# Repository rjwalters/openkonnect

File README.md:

# openkonnect

An MIT-licensed MCP server that lets an LLM agent drive a **running KiCad 10**:
schematic, layout, placement, routing, design review and manufacturing tools,
through KiCad's IPC API.

> **Status: Phase 0 bootstrap.** The MCP server runs and exposes read-only
> tools that inspect the session and the open board, plus the save, sync and
> handoff tools that write files or reload the editor (see [Tools](#tools)).
> See [ROADMAP.md](ROADMAP.md) for the plan and
> [spec/capabilities.md](spec/capabilities.md) for what each tool does.

## Quickstart

**1. Install.** You need [uv](https://docs.astral.sh/uv/) and Python 3.10 or
newer.

```bash
git clone https://github.com/rjwalters/openkonnect
cd openkonnect
uv sync
uv run openkonnect --version
```

**2. Turn on KiCad's API server.** In KiCad 10, open *Preferences > Plugins*,
check **Enable KiCad API**, and restart KiCad. The API is off by default.
Then open your board in the PCB editor. Check the connection with:

```bash
uv run openkonnect status
```

It prints `session_status` as JSON. `"ipc_reachable": true` means the server
can reach KiCad. Otherwise `reason` says what is wrong, for example
`kicad_not_running` or `ipc_disabled`.

**3. Register the server with your MCP client.** The server speaks MCP over
stdio. For Claude Code, run:

```bash
claude mcp add openkonnect -- uv run --directory /path/to/openkonnect openkonnect serve
```

For clients configured with JSON (Claude Desktop, Cursor and similar):

```json
{
  "mcpServers": {
    "openkonnect": {
      "command": "uv",
      "args": ["run", "--directory", "/path/to/openkonnect", "openkonnect", "serve"],
      "env": { "OPENKONNECT_TIMEOUT": "5" }
    }
  }
}
```

### Tools

| Tool | Spec | What it returns |
|------|------|-----------------|
| `session_status` | SES-01 | Whether KiCad is running and its API reachable, versions, instance, project directory, open documents with dirty state, and which tools this instance supports. "Not running" and "API disabled" come back as data, not errors. |
| `list_instances` | SES-02 | Every KiCad instance whose API socket can be found: endpoint, process id, whether it answered, KiCad version, open board path, and why not if it did not answer. No sockets is an empty list; a platform that cannot list sockets says `listable: false`. Sockets are probed one at a time, each bounded by the call timeout. |
| `board_summary` | LAY-01 | Live overview of the open board, unsaved changes included: path, title block, layer counts, counts of footprints, nets, tracks, vias and zones, outline size, dirty state. |
| `board_outline` | LAY-08 | The outline of the open board, unsaved changes included: the closed polygons that make it up (file frame, mm, each with a role of `outline` or `hole`), the extents, the board-frame offset and KiCad's grid and drill origins in both frames. Arcs and circles are sampled into segments. No Edge.Cuts shapes is `present: false`; shapes that do not close are `closed: false` with the open chains and the gap that defeated them, never a rectangle. |
| `list_footprints` | LAY-02 | Live list of the board's footprints, unsaved changes included: refdes, value, library ID, position (file and board frames, with the offset between them), rotation, side, locked, attributes and fields. Optional filters: `refs`, `side`, `box` (frame required), `selected_only`; a filter matching nothing is an empty list. |
| `footprint_pads` | LAY-03 | Live pads of the footprints named in `refs` (`R1` for all its pads, `R1.2` for one), unsaved changes included: `REF.PAD`, number, net, position (file and board frames, with the offset), layers, shape and size. An unknown reference or pad is `not_found`; a net that cannot be read is `net: null` with `net_state: "unknown"` and a reason, never unconnected. |
| `get_selection` | SES-08 | What is selected in the PCB editor, as file-level references `kct` accepts (reference designators, `REF.PAD`, nets), plus other items with session-scoped ids and the selection's bounding box. An empty selection is an ordinary result. |
| `list_nets` | LAY-04 | The nets on the open board with each net's net class and pad count; optional glob `pattern` and `net_class` filters. `include_items` adds the items on each net (pads as `REF.PAD`, other copper with session ids) and needs KiCad 10.0.1, else `unsupported_on_this_kicad`. |
| `list_zones` | LAY-06 | The copper zones and rule areas on the open board, unsaved changes included: session id, name, net, layers, priority, pad-connection style, filled and locked state; a rule area also lists what it keeps out. Optional `net` and `layer` filters; a filter matching nothing is an empty list, an unknown layer is `invalid_argument`. |
| `show_findings` | SES-09 | Selects in the editor the items that kicad-tools findings (`kct ... --format json`) point at, and reports per finding what resolved, what did not and why, and which findings may be stale. |
| `save_before_external_write` | SES-04 | Before a `kct` command touches the open board: each document's state before, the action taken (none, saved or refused), and the file and editor hashes to pass to `sync_from_disk`. Refuses a dirty or unknown board unless `allow_save`. See [the handoff protocol](docs/handoff-protocol.md). |
| `sync_from_disk` | SES-05 | After a `kct` command wrote the board: per document, whether the editor was reloaded from the file and whether unsaved changes were discarded. Refuses, changing nothing, when the editor may hold unsaved work, unless `discard_unsaved`. See [the handoff protocol](docs/handoff-protocol.md). |
| `run_kct_handoff` | SES-06 | Runs one allow-listed `kct` write command on the open board through the whole protocol (check, save, run, reload only on success) and reports each step and the command's result. See [the handoff protocol](docs/handoff-protocol.md). |

On KiCad 10, `dirty` is always `"unknown"` with `dirty_basis: "none"`: KiCad
10's API cannot report unsaved changes. Treat `unknown` as dirty.

Every failure is a structured error (`code`, `message`, `retryable`,
`details`), and every result carries `meta` with the time bound used and the
number of busy retries.

| Setting | Flag | Environment | Default |
|---------|------|-------------|---------|
| Bound on one tool call (s) | `--timeout` | `OPENKONNECT_TIMEOUT` | 5 |
| Bound on one IPC request (s) | `--request-timeout` | `OPENKONNECT_REQUEST_TIMEOUT` | 2 |
| Retries when KiCad is busy | `--busy-retries` | `OPENKONNECT_BUSY_RETRIES` | 3 |
| API socket | `--socket` | `OPENKONNECT_SOCKET` | discovered |

### Development

```bash
uv run ruff check . && uv run ruff format --check .
uv run pytest -rs
```

Unit tests run against a fake IPC backend. Tests marked `live_kicad` drive
the open KiCad editor (they save, reload and change its selection), so they
are skipped unless pytest is given `--live`, whatever `-m` filter or test path
is passed; `uv run pytest -rs` (and CI) runs every other test and lists them as
skipped. To run them, start KiCad 10 with the API on and the fixture board
each test names open (`tests/fixtures/board.kicad_pcb`, or
`tests/fixtures/selection.kicad_pcb` for the selection test), then run
`uv run pytest --live -m live_kicad -rs`. With `--live` they still skip when
KiCad is not reachable or the wrong board is open.

## Why this exists

In October 2026 the open-source AGPL KiCad agent plugin *Konnect* was archived,
and development moved to a commercial, closed-source successor. openkonnect is
an independent, **clean-room** implementation of the same kind of tool, under
a permissive license, so that a free live-editor agent interface for KiCad
stays available.

**openkonnect is not affiliated with, endorsed by, or derived from Konnect,
Konnect-EDA or Orchis.ai LLC.** It contains none of their code. See
[CLEANROOM.md](CLEANROOM.md) for how that is kept true.

## Design

- **Python**, built on [kicad-tools](https://github.com/rjwalters/kicad-tools)
  (MIT). File-level work (parsing, checks, netlists, exports) comes from
  kicad-tools. openkonnect adds what needs a live editor: the IPC session,
  selection and view state, and interactive edits in an open board or schematic.
- **KiCad 10 IPC API** for the live editor, through KiCad's official
  `kicad-python` bindings (MIT; see [docs/ipc-client.md](docs/ipc-client.md)).
  No `pcbnew` SWIG bindings.
- **MCP** as the agent interface, usable from any MCP client.

## License

MIT. See [LICENSE](LICENSE). Third-party code reused with attribution is
listed in [NOTICE](NOTICE).

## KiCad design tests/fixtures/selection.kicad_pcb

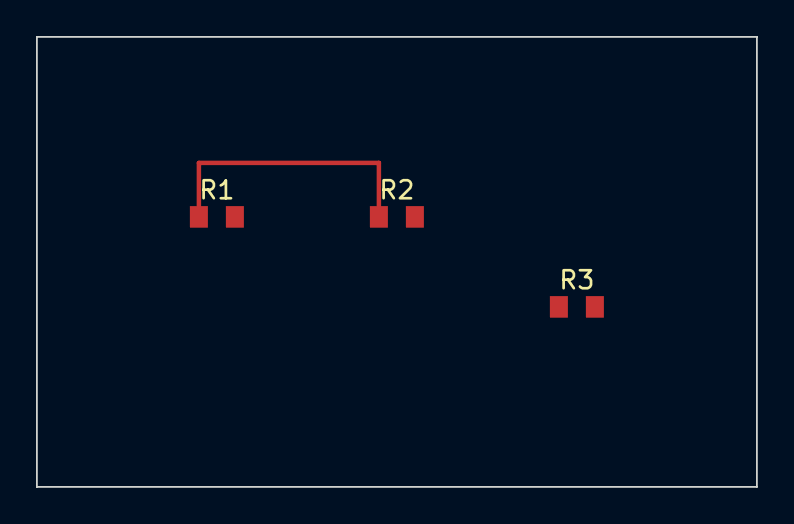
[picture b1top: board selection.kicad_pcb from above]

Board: 2 copper layers, 40.0 x 25.0 mm, 3 parts (0 on the bottom side), 3 nets.

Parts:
R1, R2: 10k; R_Fixture
R3: 1k; R_Fixture

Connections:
GND: R1.2, R3.2
SIG: R2.2, R3.1
VIN: R1.1, R2.1
